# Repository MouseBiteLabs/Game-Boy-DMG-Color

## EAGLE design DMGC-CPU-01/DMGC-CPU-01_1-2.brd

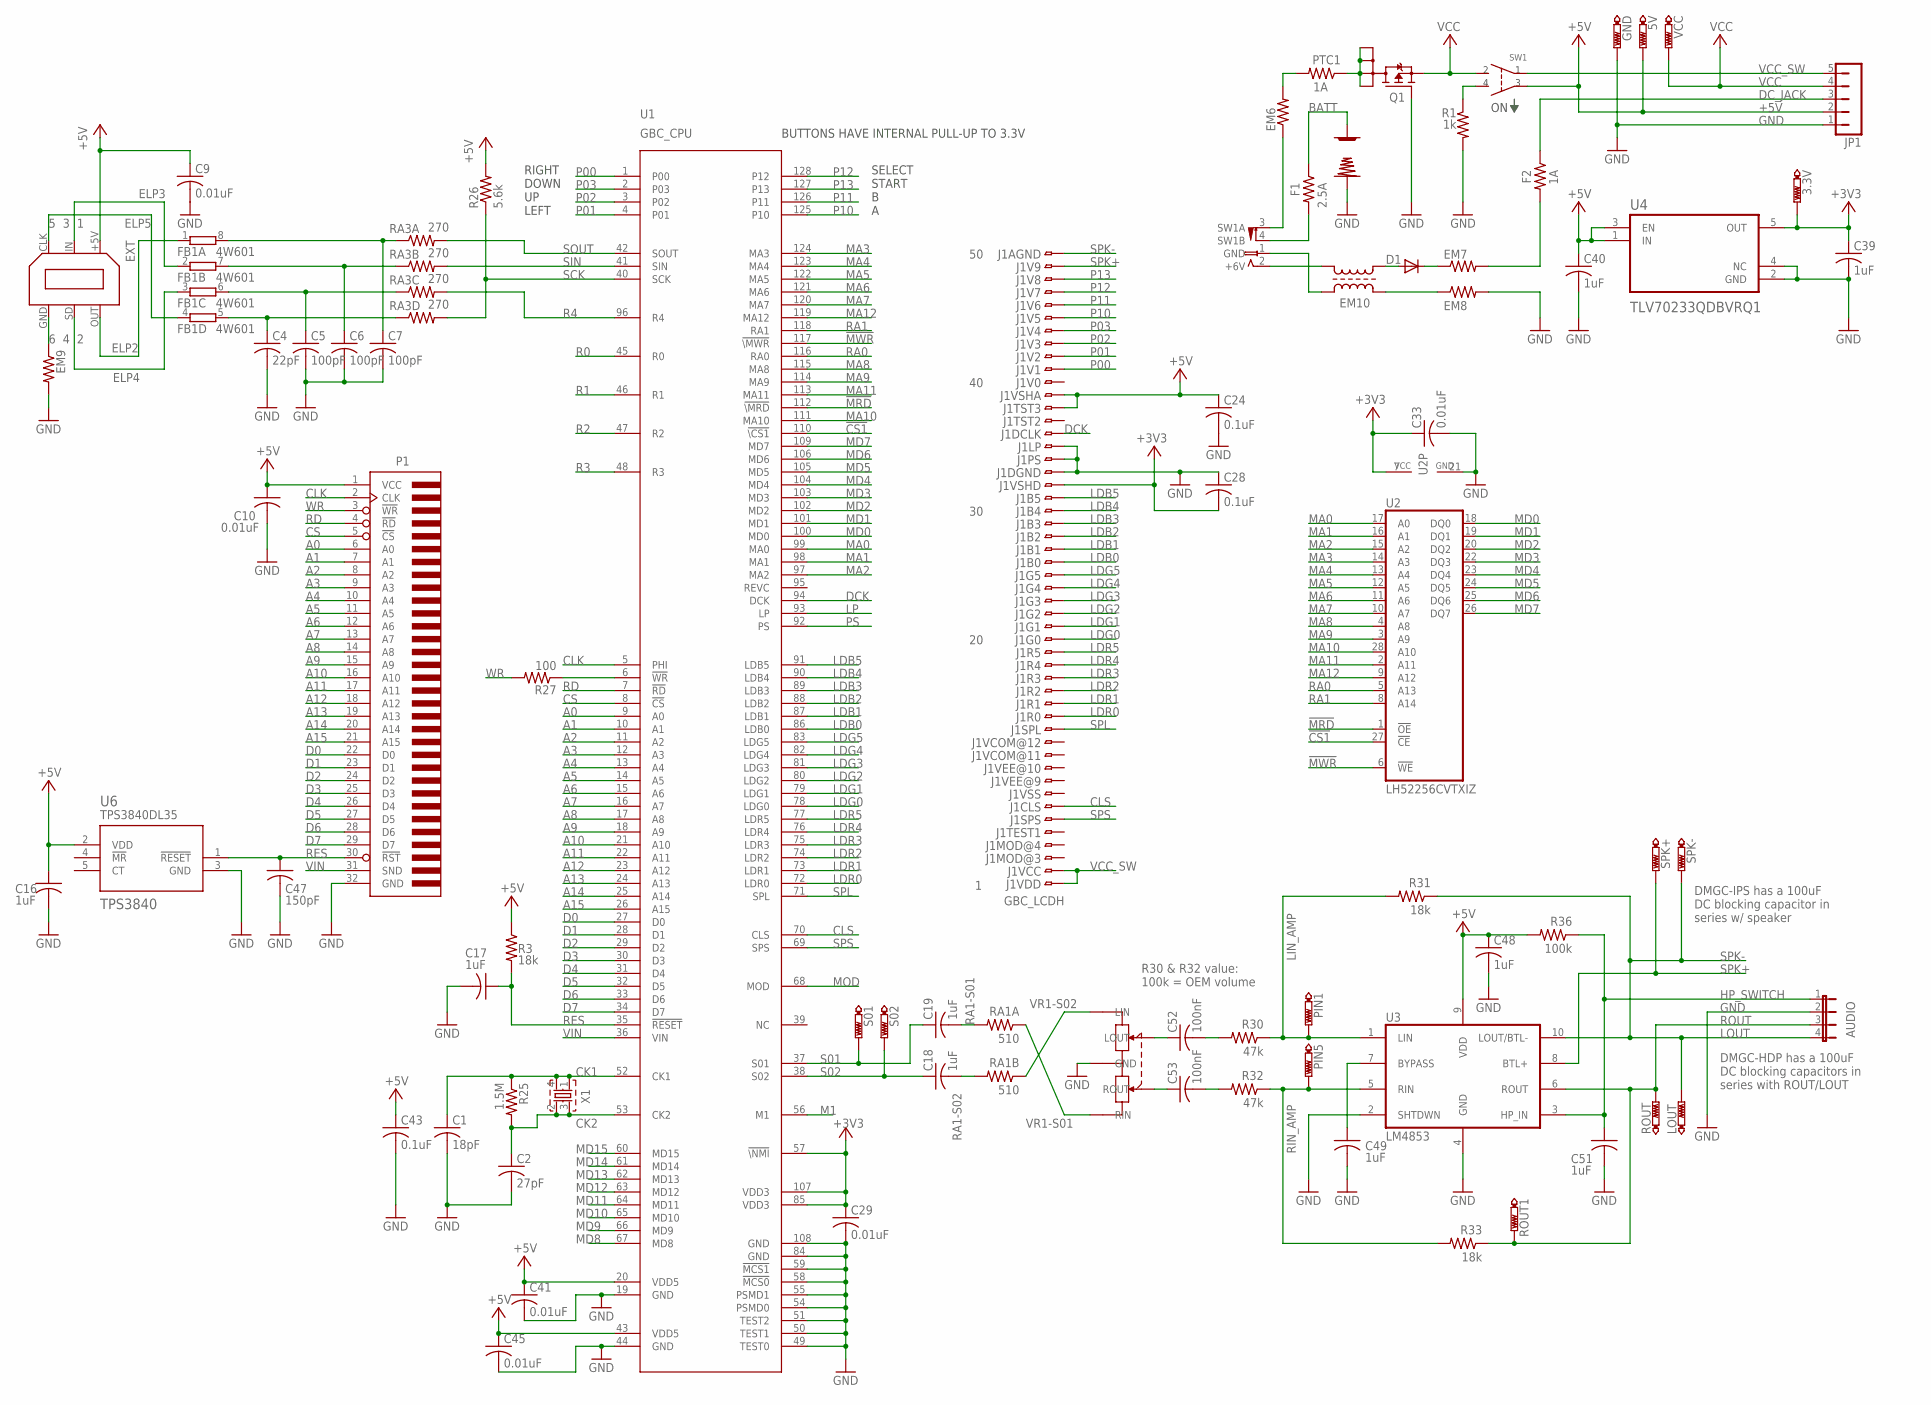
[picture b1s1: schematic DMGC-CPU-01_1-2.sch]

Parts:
3.3V, 5V: PTR1B1,27; B1,27
+: DMG+BATTERY
-: DMG-BATTERY
AUDIO: JP4E; JP4
C1: 18pF; C0603
C2: 27pF; C0603
C4: 22pF; C0603
C5, C6, C7: 100pF; C0603
C9, C10, C29, C33, C41, C45: 0.01uF; C0603
C16, C17, C18, C19, C39, C40, C48, C49, C51: 1uF; C0603
C24, C28, C43: 0.1uF; C0603
C47: 150pF; C0603
C52, C53: 100nF; C0603
D1: CGRM4001-G; SOD-123_MINI-SMA
DCJACK: DMG-PWRJACKNOHOLE; DMG-PWRJACK_NOHOLE
EM6, EM7, EM8: BLM21P221SG; R0805
EM9: BLM21P221SG; R0603
EM10: ACM4532-801-2PA; ACM4532
EXT: LINKPORTDMG-LINK-SHORT; DMG-LINK
F1: 2.5A; R1206
F2: 1A; R1206
FB1: 4W601; EXB38V
GND: PTR1B1,27; B1,27
J1: GBC_LCDH; FH12-50S-0.5SH
JP1: JP5
LOUT: PTR1B1,27; B1,27
P1: GBCONN
PIN1, PIN5: PTR1B1,27; B1,27
PTC1: 1A; R1206
Q1: SI1401EDH; SOT363_INFINEON
R1: 1k; R0603
R3, R31, R33: 18k; R0603
R25: 1.5M; R0603
R26: 5.6k; R0603
R27: 100; R0603
R30, R32: 47k; R0603
R36: 100k; R0603
RA1A, RA1B: 510; R0603
RA3A, RA3B, RA3C, RA3D: 270; R0603
ROUT, ROUT1: PTR1B1,27; B1,27
S01, S02: PTR1B1,27; B1,27
SPK+: PTR1B1,27; B1,27
SPK-: PTR1B1,27; B1,27
SW1: DMG-SW; DMG-SWITCH
U1: GBC_CPU; QFP-128
U2: LH52256CVTXIZ; TSOP1-28
U3: LM4853; VSSOP10
U4: TLV70233QDBVRQ1; SOT95P280X145-5N
U6: TPS3840; SOT-23-5
VCC: PTR1B1,27; B1,27
VR1: 10K; DMG-POT
X1: 8.388608MHZ12SMX-B-4-PAD; 7.5X5-4-PAD

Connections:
!CS1: U1.110 (!\CS1), U2.27 (!CE)
!MRD: U1.112 (!\MRD), U2.1 (!OE)
!MWR: U1.117 (!\MWR), U2.6 (!WE)
+3V3: 3.3V.TP, C28.2, C29.1, C33.1, C39.1, J1.32, U1.57 (!\NMI), U1.85 (VDD3), U1.107 (VDD3), U2.7 (VCC), U4.5 (OUT)
+5V: 5V.TP, C9.1, C10.1, C16.1, C24.1, C40.1, C41.1, C43.1, C45.1, C48.1, EXT.+5V, J1.38, J1.39, JP1.2, P1.1 (VCC), R3.1, R26.2, R36.2, SW1.P$3 (3), U1.20 (VDD5), U1.43 (VDD5), U3.9 (VDD), U4.1 (IN), U4.3 (EN), U6.2 (VDD)
A0: P1.6 (A0), U1.9 (A0)
A1: P1.7 (A1), U1.10 (A1)
A2: P1.8 (A2), U1.11 (A2)
A3: P1.9 (A3), U1.12 (A3)
A4: P1.10 (A4), U1.13 (A4)
A5: P1.11 (A5), U1.14 (A5)
A6: P1.12 (A6), U1.15 (A6)
A7: P1.13 (A7), U1.16 (A7)
A8: P1.14 (A8), U1.17 (A8)
A9: P1.15 (A9), U1.18 (A9)
A10: P1.16 (A10), U1.21 (A10)
A11: P1.17 (A11), U1.22 (A11)
A12: P1.18 (A12), U1.23 (A12)
A13: P1.19 (A13), U1.24 (A13)
A14: P1.20 (A14), U1.25 (A14)
A15: P1.21 (A15), U1.26 (A15)
BATT: +.P$1, F1.1
BATT_DC: DCJACK.3 (SW1A), EM6.1
CK1: C1.1, R25.1, U1.52 (CK1), X1.1, X1.4
CK2: C2.1, R25.2, U1.53 (CK2), X1.2, X1.3
CLK: P1.2 (CLK), U1.5 (PHI)
CLS: J1.7, U1.70 (CLS)
CS: P1.5 (!CS), U1.8 (!CS)
D0: P1.22 (D0), U1.27 (D0)
D1: P1.23 (D1), U1.28 (D1)
D2: P1.24 (D2), U1.29 (D2)
D3: P1.25 (D3), U1.30 (D3)
D4: P1.26 (D4), U1.31 (D4)
D5: P1.27 (D5), U1.32 (D5)
D6: P1.28 (D6), U1.33 (D6)
D7: P1.29 (D7), U1.34 (D7)
DCK: J1.36, U1.94 (DCK)
DC_JACK: F2.1, JP1.3
ELP2: EXT.OUT, FB1.1
ELP3: EXT.IN, FB1.2 (1)
ELP4: EXT.SD, FB1.3 (1)
ELP5: EXT.CLK, FB1.4 (1)
EM10_EM8: EM8.1, EM10.3
EM10_GND: DCJACK.1 (GND), EM10.2
EM10_POS: DCJACK.2 (+6V), EM10.1
GND: -.P$1, AUDIO.2, C1.2, C2.2, C4.2, C5.2, C6.2, C7.2, C9.2, C10.2, C16.2, C17.2, C24.2, C28.1, C29.2, C33.2, C39.2, C40.2, C41.2, C43.2, C45.2, C47.2, C48.2, C49.2, C51.2, EM8.2, EM9.2, EXT.SHIELD (GND), EXT.SHIELD1 (GND), GND.TP, J1.33, J1.34, J1.35, JP1.1, P1.32 (GND), Q1.3 (G), R1.2, SW1.P$7 (GND), SW1.P$8 (GND), U1.19 (GND), U1.44 (GND), U1.49 (TEST0), U1.50 (TEST1), U1.51 (TEST2), U1.54 (PSMD0), U1.55 (PSMD1), U1.58 (!MCS0), U1.59 (!MCS1), U1.84 (GND), U1.108 (GND), U2.21 (GND), U3.2 (SHTDWN), U3.4 (GND), U4.2 (GND), U4.4 (NC), U6.3 (GND), VR1.P$1 (GND), VR1.P$6 (GND), VR1.P$7 (GND)
HP_SWITCH: AUDIO.1, C51.1, R36.1, U3.3 (HP_IN)
LDB0: J1.26, U1.86 (LDB0)
LDB1: J1.27, U1.87 (LDB1)
LDB2: J1.28, U1.88 (LDB2)
LDB3: J1.29, U1.89 (LDB3)
LDB4: J1.30, U1.90 (LDB4)
LDB5: J1.31, U1.91 (LDB5)
LDG0: J1.20, U1.78 (LDG0)
LDG1: J1.21, U1.79 (LDG1)
LDG2: J1.22, U1.80 (LDG2)
LDG3: J1.23, U1.81 (LDG3)
LDG4: J1.24, U1.82 (LDG4)
LDG5: J1.25, U1.83 (LDG5)
LDR0: J1.14, U1.72 (LDR0)
LDR1: J1.15, U1.73 (LDR1)
LDR2: J1.16, U1.74 (LDR2)
LDR3: J1.17, U1.75 (LDR3)
LDR4: J1.18, U1.76 (LDR4)
LDR5: J1.19, U1.77 (LDR5)
LIN_AMP: PIN1.TP, R30.1, R31.2, U3.1 (LIN)
LP: U1.93 (LP)
M1: U1.56 (M1)
MA0: U1.99 (MA0), U2.17 (A0)
MA1: U1.98 (MA1), U2.16 (A1)
MA2: U1.97 (MA2), U2.15 (A2)
MA3: U1.124 (MA3), U2.14 (A3)
MA4: U1.123 (MA4), U2.13 (A4)
MA5: U1.122 (MA5), U2.12 (A5)
MA6: U1.121 (MA6), U2.11 (A6)
MA7: U1.120 (MA7), U2.10 (A7)
MA8: U1.115 (MA8), U2.4 (A8)
MA9: U1.114 (MA9), U2.3 (A9)
MA10: U1.111 (MA10), U2.28 (A10)
MA11: U1.113 (MA11), U2.2 (A11)
MA12: U1.119 (MA12), U2.9 (A12)
MD0: U1.100 (MD0), U2.18 (DQ0)
MD1: U1.101 (MD1), U2.19 (DQ1)
MD2: U1.102 (MD2), U2.20 (DQ2)
MD3: U1.103 (MD3), U2.22 (DQ3)
MD4: U1.104 (MD4), U2.23 (DQ4)
MD5: U1.105 (MD5), U2.24 (DQ5)
MD6: U1.106 (MD6), U2.25 (DQ6)
MD7: U1.109 (MD7), U2.26 (DQ7)
MD8: U1.67 (MD8)
MD9: U1.66 (MD9)
MD10: U1.65 (MD10)
MD11: U1.64 (MD11)
MD12: U1.63 (MD12)
MD13: U1.62 (MD13)
MD14: U1.61 (MD14)
MD15: U1.60 (MD15)
MOD: U1.68 (MOD)
unnamed: C7.1, FB1.8 (2), RA3A.1
unnamed: C6.1, FB1.7 (2), RA3B.1
unnamed: C52.2, R30.2
unnamed: C53.2, R32.2
unnamed: C5.1, FB1.6 (2), RA3C.1
unnamed: C52.1, VR1.P$3 (LOUT)
unnamed: R27.1, U1.6 (!WR)
unnamed: C4.1, FB1.5 (2), RA3D.1
unnamed: C53.1, VR1.P$2 (ROUT)
unnamed: R1.1, SW1.P$4 (4)
unnamed: D1.C, EM7.1
unnamed: EM7.2, F2.2
unnamed: EM6.2, PTC1.2
unnamed: EM9.1, EXT.GND
unnamed: C49.1, U3.7 (BYPASS)
P00: J1.41, U1.1 (P00)
P01: J1.42, U1.4 (P01)
P02: J1.43, U1.3 (P02)
P03: J1.44, U1.2 (P03)
P10: J1.45, U1.125 (P10)
P11: J1.46, U1.126 (P11)
P12: J1.47, U1.128 (P12)
P13: J1.48, U1.127 (P13)
PFET_DRAIN: PTC1.1, Q1.1 (D1), Q1.2 (D2), Q1.5 (D5), Q1.6 (D6)
PS: U1.92 (PS)
R0: U1.45 (R0)
R1: U1.46 (R1)
R2: U1.47 (R2)
R3: U1.48 (R3)
R4: RA3C.2, U1.96 (R4)
RA0: U1.116 (RA0), U2.5 (A13)
RA1: U1.118 (RA1), U2.8 (A14)
RA1-S01: C19.2, RA1A.2
RA1-S02: C18.2, RA1B.2
RD: P1.4 (!RD), U1.7 (!RD)
RES: C17.1, C47.1, P1.30 (!RST), R3.2, U1.35 (!RESET), U6.1 (!RESET)
RIN_AMP: PIN5.TP, R32.1, R33.2, U3.5 (RIN)
ROUT: AUDIO.3, R33.1, ROUT.TP, ROUT1.TP, U3.6 (ROUT)
RPP: D1.A, EM10.4
S01: C19.1, S01.TP, U1.37 (S01)
S02: C18.1, S02.TP, U1.38 (S02)
SCK: R26.1, RA3D.2, U1.40 (SCK)
SIN: RA3B.2, U1.41 (SIN)
SOUT: RA3A.2, U1.42 (SOUT)
SPK+: J1.49, SPK+.TP, U3.8 (BTL+)
SPK-: AUDIO.4, J1.50, LOUT.TP, R31.1, SPK-.TP, U3.10 (LOUT/BTL-)
SPL: J1.13, U1.71 (SPL)
SPS: J1.6, U1.69 (SPS)
SW1B: DCJACK.4 (SW1B), F1.2
VCC: JP1.4, Q1.4 (S), SW1.P$2 (2), VCC.TP
VCC_SW: J1.1, J1.2, JP1.5, SW1.P$1 (1)
VIN: P1.31 (SND), U1.36 (VIN)
VR1-S01: RA1A.1, VR1.P$5 (RIN)
VR1-S02: RA1B.1, VR1.P$4 (LIN)
WR: P1.3 (!WR), R27.2

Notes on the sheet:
5 3 1
6 4 2
BUTTONS HAVE INTERNAL PULL-UP TO 3.3V
SELECT START B A
RIGHT DOWN UP LEFT
TPS3840DL35
R30 & R32 value: 100k = OEM volume
LOUT
DMGC-IPS has a 100uF DC blocking capacitor in series w/ speaker
DMGC-HDP has a 100uF DC blocking capacitors in series with ROUT/LOUT

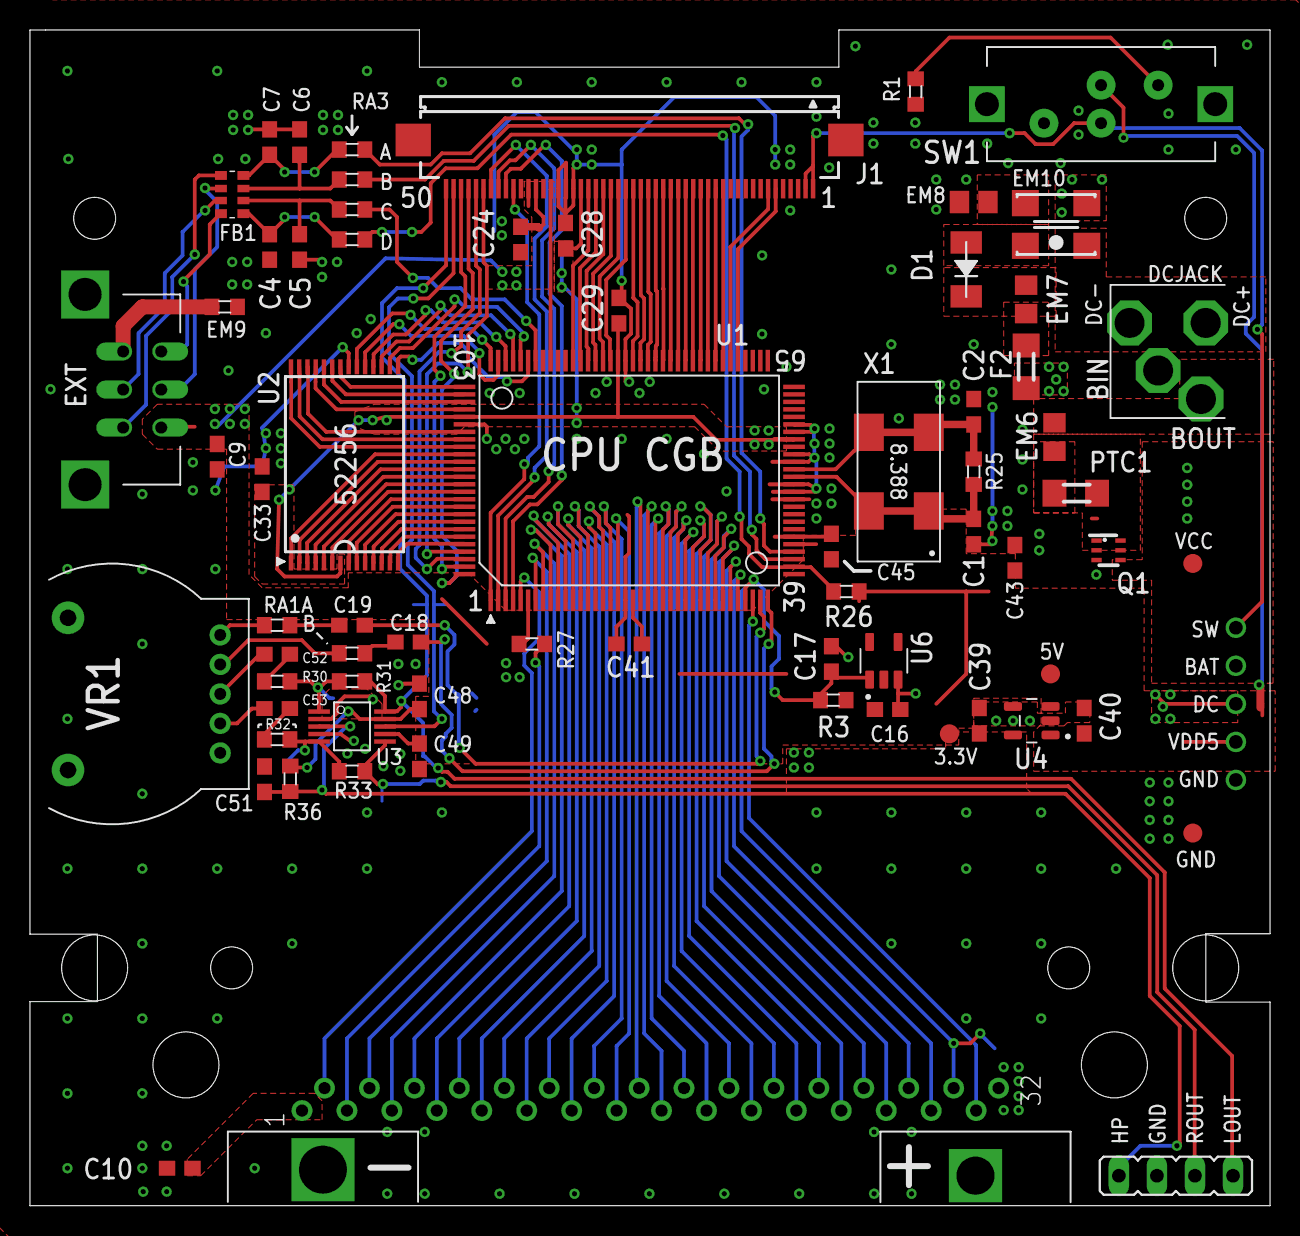
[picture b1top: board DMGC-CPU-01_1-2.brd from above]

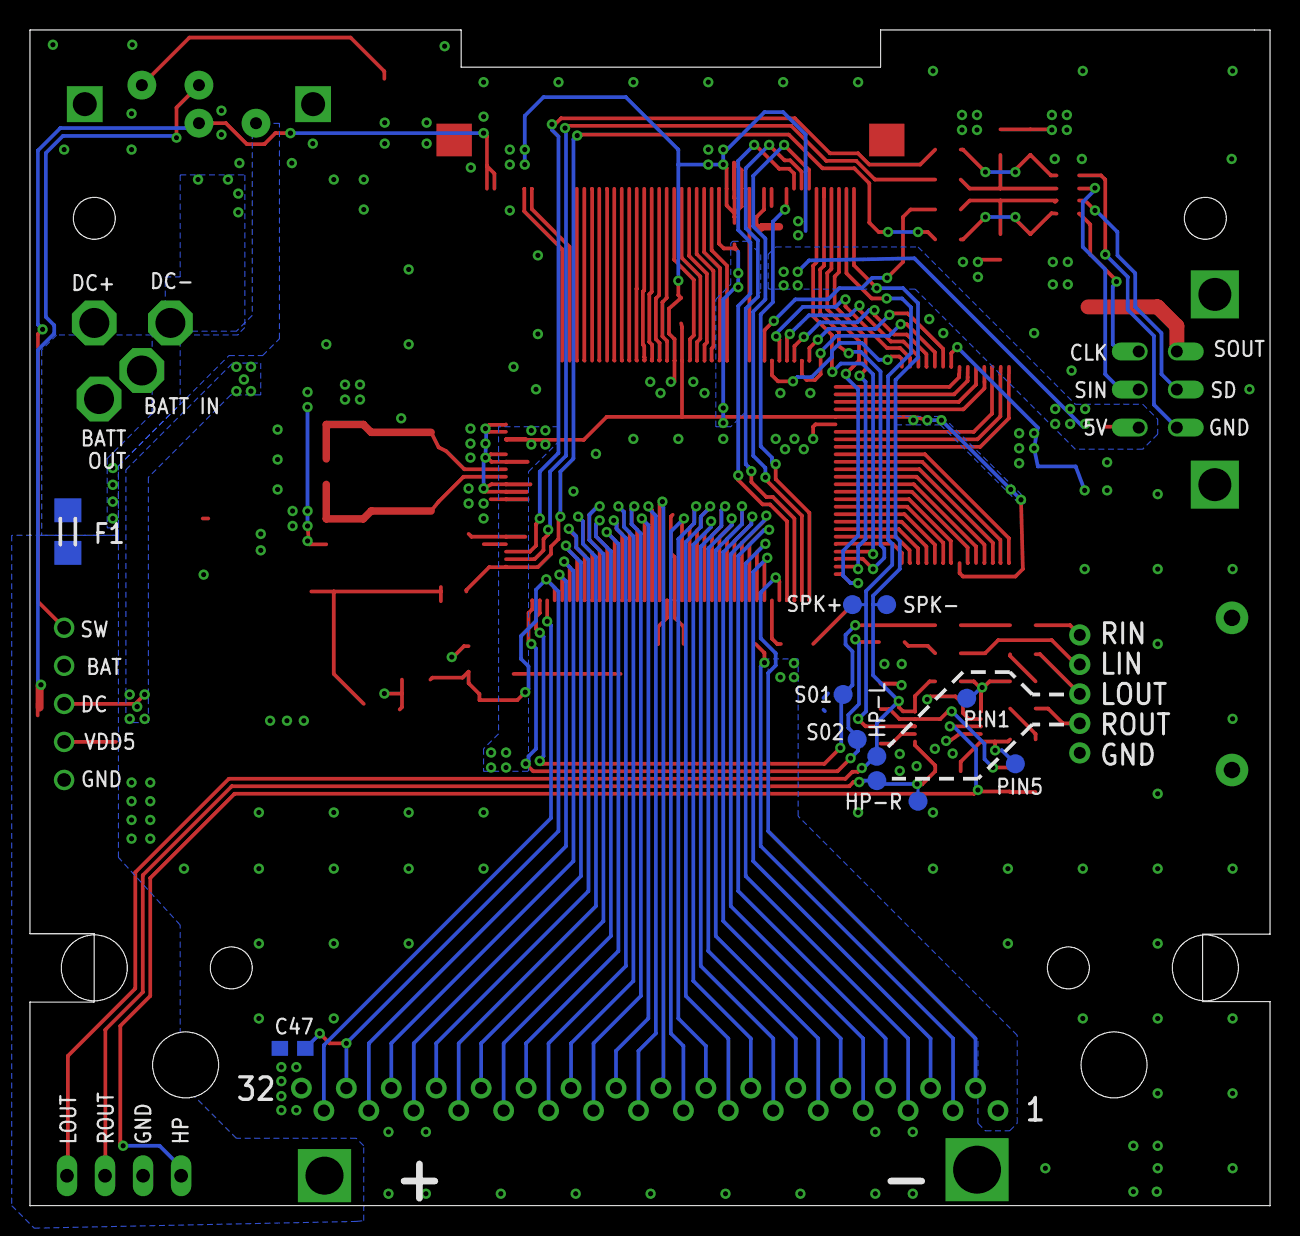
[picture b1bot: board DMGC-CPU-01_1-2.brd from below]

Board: 2 copper layers, 82.8 x 78.5 mm, 83 parts (11 on the bottom side), 137 nets.

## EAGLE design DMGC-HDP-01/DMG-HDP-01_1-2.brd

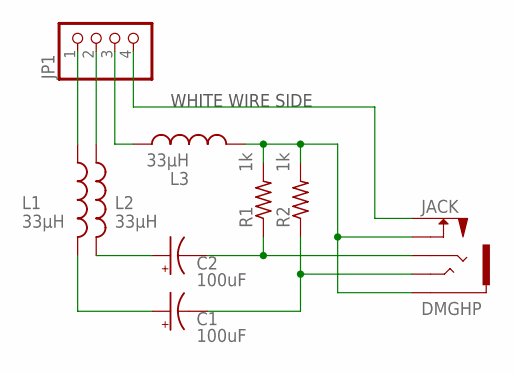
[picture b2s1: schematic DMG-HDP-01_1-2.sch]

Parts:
C1, C2: 100uF; E2,5-5
JACK: DMGHP; DMG-HEADPHONE
JP1: PINHD-1X4; 1X04
L1, L2, L3: 33µH; 0204/7
R1, R2: 1k; R0603

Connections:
unnamed: JP1.1, L1.1
unnamed: JP1.3, L3.1
unnamed: JP1.2, L2.1
unnamed: C1.+, L1.2
unnamed: C2.+, L2.2
unnamed: JACK.GND (S), JACK.SWGND (SWB), L3.2, R1.2, R2.2
unnamed: JACK.SW (SWA), JP1.4
unnamed: C2.-, JACK.R, R1.1
unnamed: C1.-, JACK.T, R2.1

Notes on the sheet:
WHITE WIRE SIDE

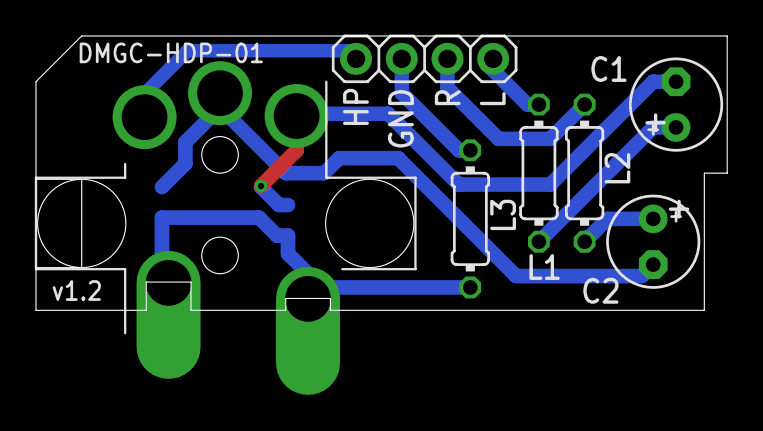
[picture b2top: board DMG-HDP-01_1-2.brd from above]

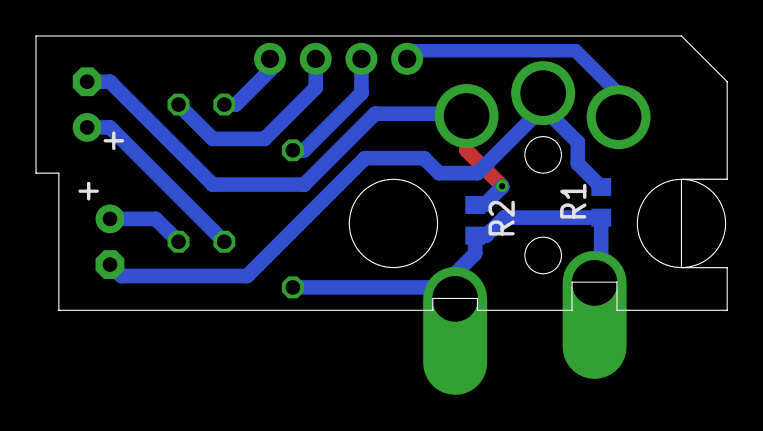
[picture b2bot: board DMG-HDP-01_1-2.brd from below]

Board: 2 copper layers, 38.4 x 15.2 mm, 9 parts (2 on the bottom side), 9 nets.

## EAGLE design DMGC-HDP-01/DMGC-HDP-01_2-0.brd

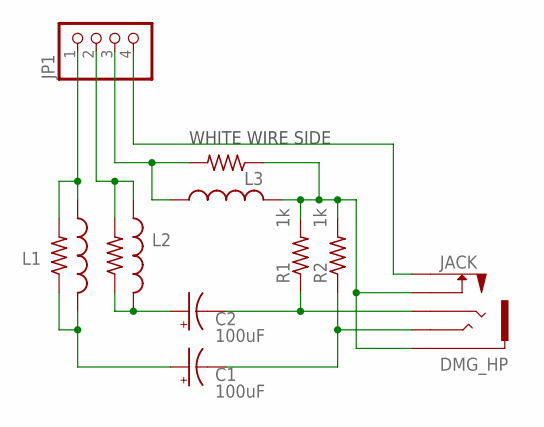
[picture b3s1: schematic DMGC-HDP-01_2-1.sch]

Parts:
C1, C2: 100uF; E2,5-5
EM1, EM2, EM9: BLM21P221SG; R0603
JACK: DMG_HP
JP1: PINHD-1X4; 1X04
L1, L2, L3: 33µH; 0204/7
R1, R2: 1k; R0603

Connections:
unnamed: EM9.2, JP1.1, L1.1
unnamed: EM2.2, JP1.3, L3.1
unnamed: EM1.2, JP1.2, L2.1
unnamed: C1.+, EM9.1, L1.2
unnamed: C2.+, EM1.1, L2.2
unnamed: EM2.1, JACK.GND (S), JACK.SWGND (SWB), L3.2, R1.2, R2.2
unnamed: JACK.SW (SWA), JP1.4
unnamed: C2.-, JACK.R, R1.1
unnamed: C1.-, JACK.T, R2.1

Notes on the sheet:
WHITE WIRE SIDE

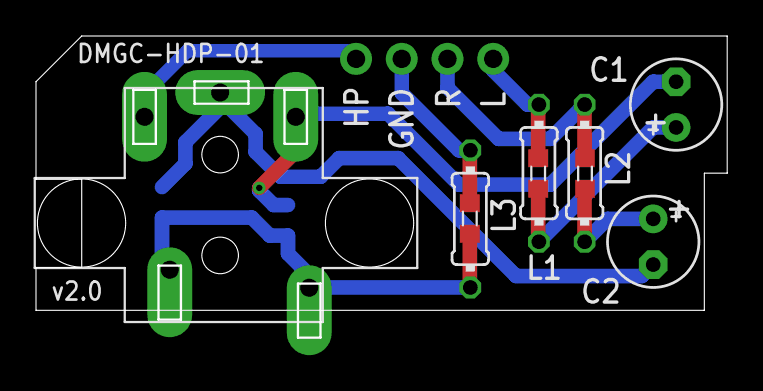
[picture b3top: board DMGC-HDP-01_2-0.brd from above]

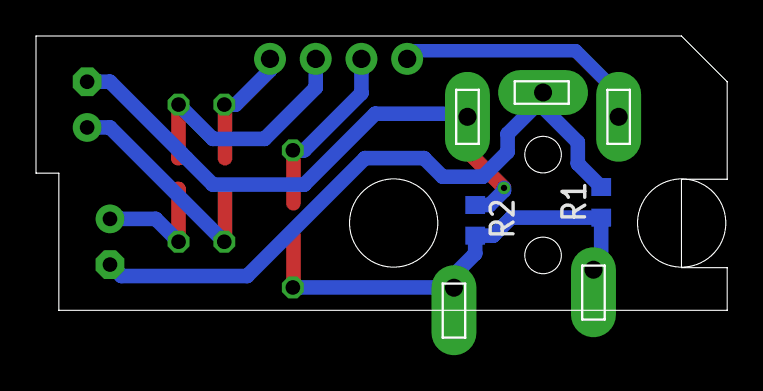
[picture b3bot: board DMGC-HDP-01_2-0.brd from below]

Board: 2 copper layers, 38.4 x 16.8 mm, 12 parts (2 on the bottom side), 9 nets.
